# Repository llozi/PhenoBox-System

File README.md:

# Fork of the original PhenoBox-System repo of the Gregor-Mendel-Institute
[Original Repo](https://github.com/Gregor-Mendel-Institute/PhenoBox-System "PhenoBox-System, Gregor-Mendel-Institute")

Changes include the design of a printed circuit board to interface the Raspberry Pi (fully electronic,
no electro-mechanical elements) to facilitate the wiring.

The interface board includes a MOSFET switch for controlling the illumination. It may be used to on/off switch 
or even control the illumination intensity using PWM.

The interface board requires a few changes in the assignment of the GPIO lines.

A few simple python scripts have been added to test the workings of the interface board.

For more details on the modifications check [this fork's Wiki](https://github.com/llozi/PhenoBox-System/wiki).

Below follows the original README.md.

# PhenoBox-System
The “Phenobox”, a flexible, automated, open-source plant phenotyping solution

This is the home of all the source code for our PhenoBox/PhenoPipe system. 

Original Publication: https://nph.onlinelibrary.wiley.com/doi/abs/10.1111/nph.15129

This project is still under developement and we have already planned many improvements.
If you encounter any problems feel free to contribute to this project and help us create a great open source phenotyping solution.

For further reference please use the Wiki pages of this repository. If you have any issues either use the Github Issue page or write an email to sebastian.seitner@vbcf.ac.at

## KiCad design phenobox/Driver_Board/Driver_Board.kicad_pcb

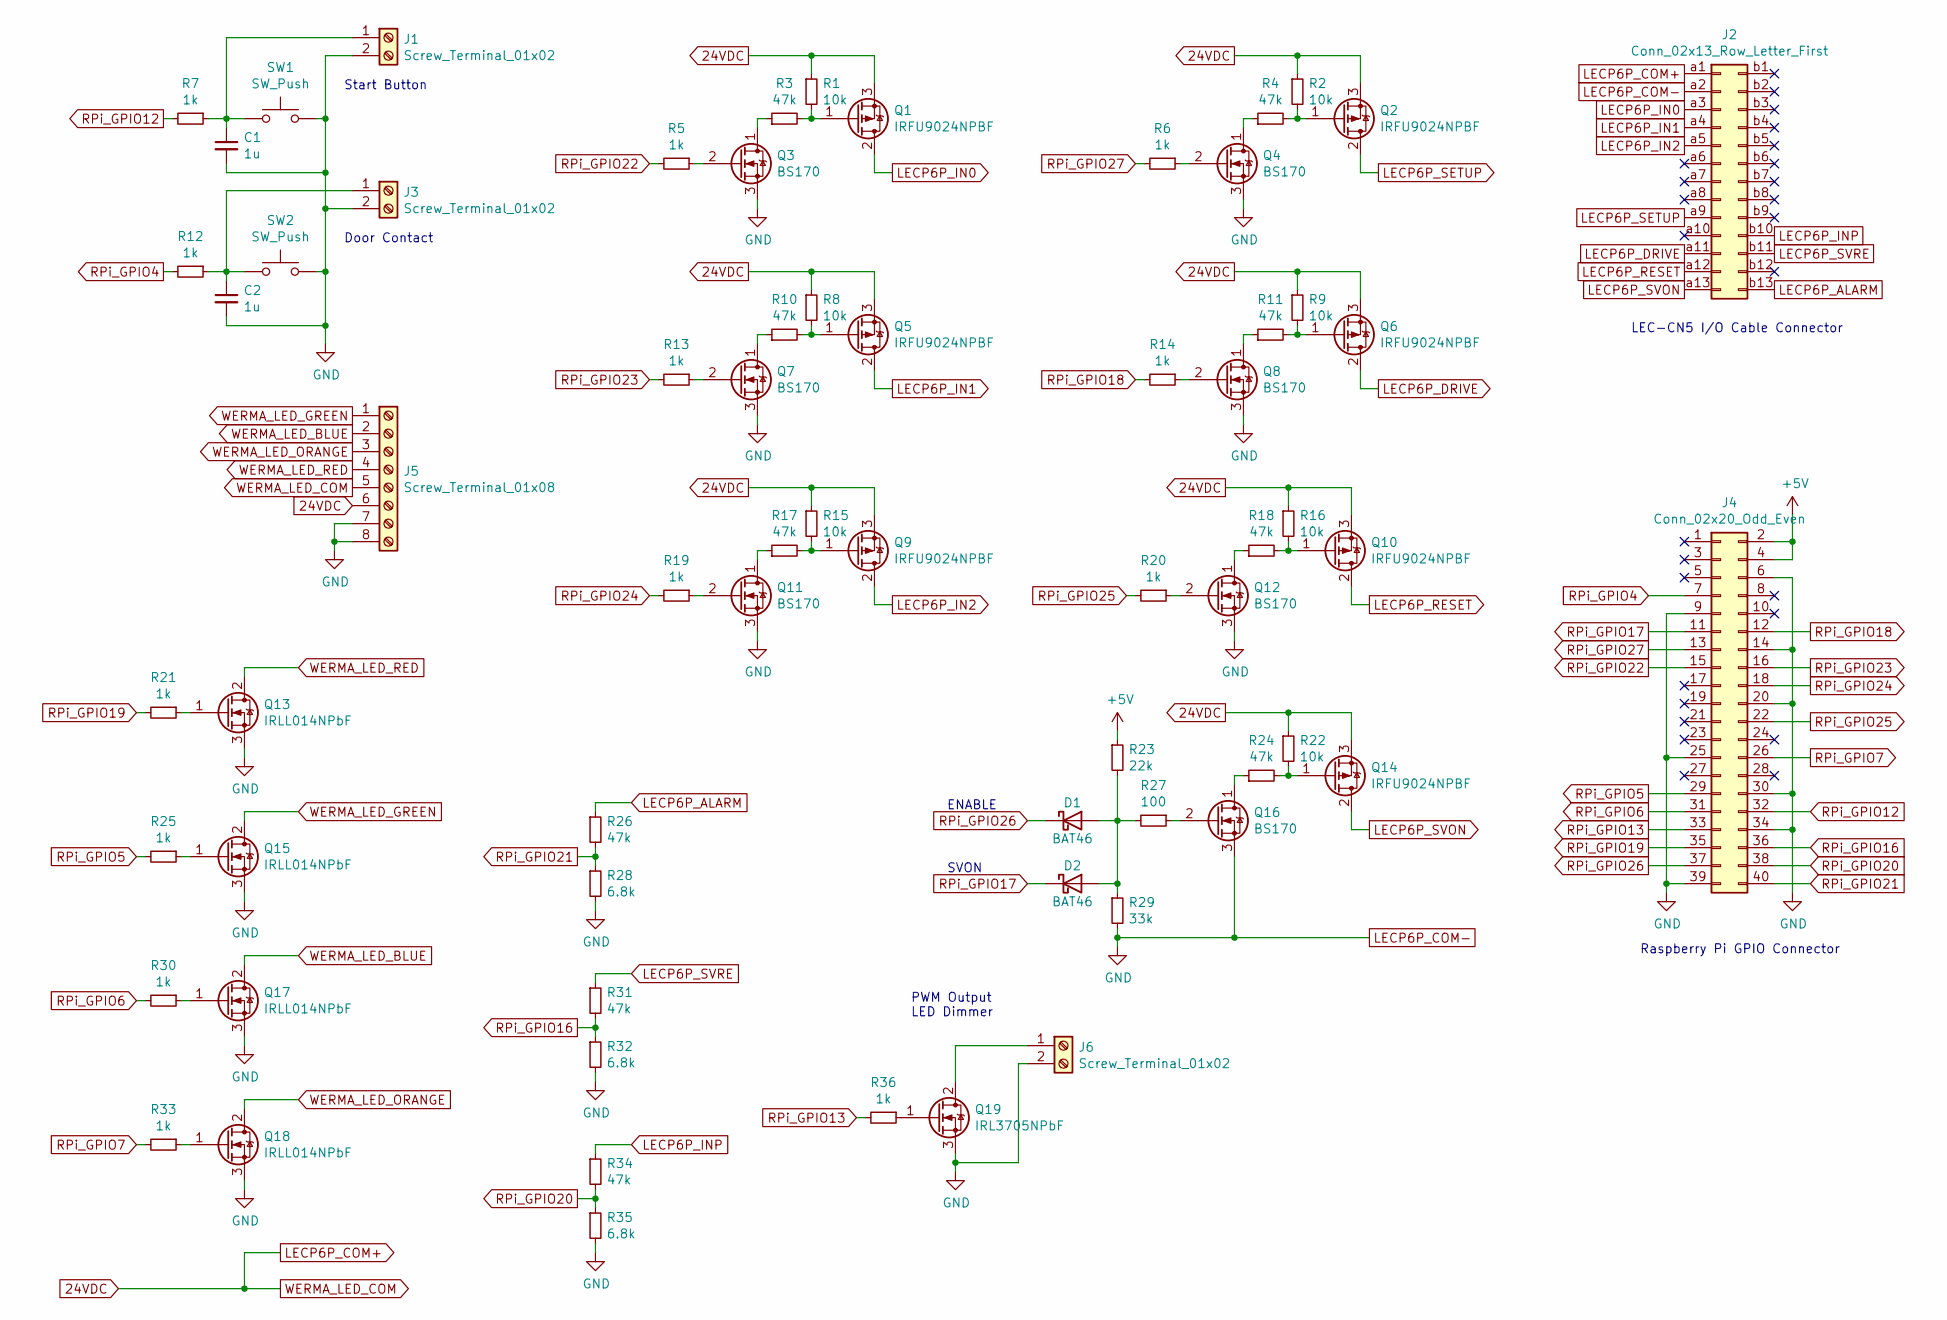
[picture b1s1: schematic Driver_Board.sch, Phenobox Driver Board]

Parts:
C1, C2: 1u; C_Rect_L4.0mm_W2.5mm_P2.50mm
D1, D2: BAT46; D_DO-35_SOD27_P7.62mm_Horizontal
J1, J3, J6: Screw_Terminal_01x02; TerminalBlock_Phoenix_MKDS-1,5-2-5.08_1x02_P5.08mm_Horizont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
J2: Conn_02x13_Row_Letter_First; IDC-Header_2x13_P2.54mm_Vertical
J4: Conn_02x20_Odd_Even; IDC-Header_2x20_P2.54mm_Vertical
J5: Screw_Terminal_01x08; TerminalBlock_Phoenix_MKDS-1,5-8-5.08_1x08_P5.08mm_Horizont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
Q1, Q2, Q5, Q6, Q9, Q10, Q14: IRFU9024NPBF; TO-251-3_Vertical
Q3, Q4, Q7, Q8, Q11, Q12, Q16: BS170; TO-92_Wide
Q13, Q15, Q17, Q18: IRLL014NPbF; SOT-223-3_TabPin2
Q19: IRL3705NPbF; TO-220-3_Vertical
R1, R2, R8, R9, R15, R16, R22: 10k; R_Axial_DIN0207_L6.3mm_D2.5mm_P7.62mm_Horizontal
R3, R4, R10, R11, R17, R18, R24, R26, R31, R34: 47k; R_Axial_DIN0207_L6.3mm_D2.5mm_P7.62mm_Horizontal
R5, R6, R7, R12, R13, R14, R19, R20, R21, R25, R30, R33, R36: 1k; R_Axial_DIN0207_L6.3mm_D2.5mm_P7.62mm_Horizontal
R23: 22k; R_Axial_DIN0207_L6.3mm_D2.5mm_P7.62mm_Horizontal
R27: 100; R_Axial_DIN0207_L6.3mm_D2.5mm_P7.62mm_Horizontal
R28, R32, R35: 6.8k; R_Axial_DIN0207_L6.3mm_D2.5mm_P7.62mm_Horizontal
R29: 33k; R_Axial_DIN0207_L6.3mm_D2.5mm_P7.62mm_Horizontal
SW1, SW2: SW_Push

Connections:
24VDC: J2.a1, J5.5, J5.6, Q1.3 (S), Q2.3 (S), Q5.3 (S), Q6.3 (S), Q9.3 (S), Q10.3 (S), Q14.3 (S), R1.1, R2.1, R8.1, R9.1, R15.1, R16.1, R22.1
+5V: J4.2, J4.4, R23.1
LECP6P_ALARM: J2.b13, R26.1
LECP6P_COM-: C1.2, C2.2, J1.2, J2.a2, J3.2, J4.6, J4.9, J4.14, J4.20, J4.25, J4.30, J4.34, J4.39, J5.7, J5.8, J6.2, Q3.3 (S), Q4.3 (S), Q7.3 (S), Q8.3 (S), Q11.3 (S), Q12.3 (S), Q13.3 (S), Q15.3 (S), Q16.3 (S), Q17.3 (S), Q18.3 (S), Q19.3 (S), R28.2, R29.2, R32.2, R35.2, SW1.2, SW2.2
LECP6P_DRIVE: J2.a11, Q6.2 (D)
LECP6P_IN0: J2.a3, Q1.2 (D)
LECP6P_IN1: J2.a4, Q5.2 (D)
LECP6P_IN2: J2.a5, Q9.2 (D)
LECP6P_INP: J2.b10, R34.1
LECP6P_RESET: J2.a12, Q10.2 (D)
LECP6P_SETUP: J2.a9, Q2.2 (D)
LECP6P_SVON: J2.a13, Q14.2 (D)
LECP6P_SVRE: J2.b11, R31.1
unnamed: C1.1, J1.1, R7.1, SW1.1
unnamed: C2.1, J3.1, R12.1, SW2.1
unnamed: D1.2 (A), D2.2 (A), R23.2, R27.2, R29.1
unnamed: J6.1, Q19.2 (D)
unnamed: Q1.1 (G), R1.2, R3.2
unnamed: Q2.1 (G), R2.2, R4.2
unnamed: Q3.1 (D), R3.1
unnamed: Q3.2 (G), R5.1
unnamed: Q4.1 (D), R4.1
unnamed: Q4.2 (G), R6.1
unnamed: Q5.1 (G), R8.2, R10.2
unnamed: Q6.1 (G), R9.2, R11.2
unnamed: Q7.1 (D), R10.1
unnamed: Q7.2 (G), R13.1
unnamed: Q8.1 (D), R11.1
unnamed: Q8.2 (G), R14.1
unnamed: Q9.1 (G), R15.2, R17.2
unnamed: Q10.1 (G), R16.2, R18.2
unnamed: Q11.1 (D), R17.1
unnamed: Q11.2 (G), R19.1
unnamed: Q12.1 (D), R18.1
unnamed: Q12.2 (G), R20.1
unnamed: Q13.1 (G), R21.1
unnamed: Q14.1 (G), R22.2, R24.2
unnamed: Q15.1 (G), R25.1
unnamed: Q16.1 (D), R24.1
unnamed: Q16.2 (G), R27.1
unnamed: Q17.1 (G), R30.1
unnamed: Q18.1 (G), R33.1
unnamed: Q19.1 (G), R36.1
RPi_GPIO4: J4.7, R12.2
RPi_GPIO5: J4.29, R25.2
RPi_GPIO6: J4.31, R30.2
RPi_GPIO7: J4.26, R33.2
RPi_GPIO12: J4.32, R7.2
RPi_GPIO13: J4.33, R36.2
RPi_GPIO16: J4.36, R31.2, R32.1
RPi_GPIO17: D2.1 (K), J4.11
RPi_GPIO18: J4.12, R14.2
RPi_GPIO19: J4.35, R21.2
RPi_GPIO20: J4.38, R34.2, R35.1
RPi_GPIO21: J4.40, R26.2, R28.1
RPi_GPIO22: J4.15, R5.2
RPi_GPIO23: J4.16, R13.2
RPi_GPIO24: J4.18, R19.2
RPi_GPIO25: J4.22, R20.2
RPi_GPIO26: D1.1 (K), J4.37
RPi_GPIO27: J4.13, R6.2
WERMA_LED_BLUE: J5.2, Q17.2 (D)
WERMA_LED_GREEN: J5.1, Q15.2 (D)
WERMA_LED_ORANGE: J5.3, Q18.2 (D)
WERMA_LED_RED: J5.4, Q13.2 (D)

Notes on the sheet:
Start Button
Door Contact
SVON
ENABLE
LEC-CN5 I/O Cable Connector
Raspberry Pi GPIO Connector
PWM Output LED Dimmer

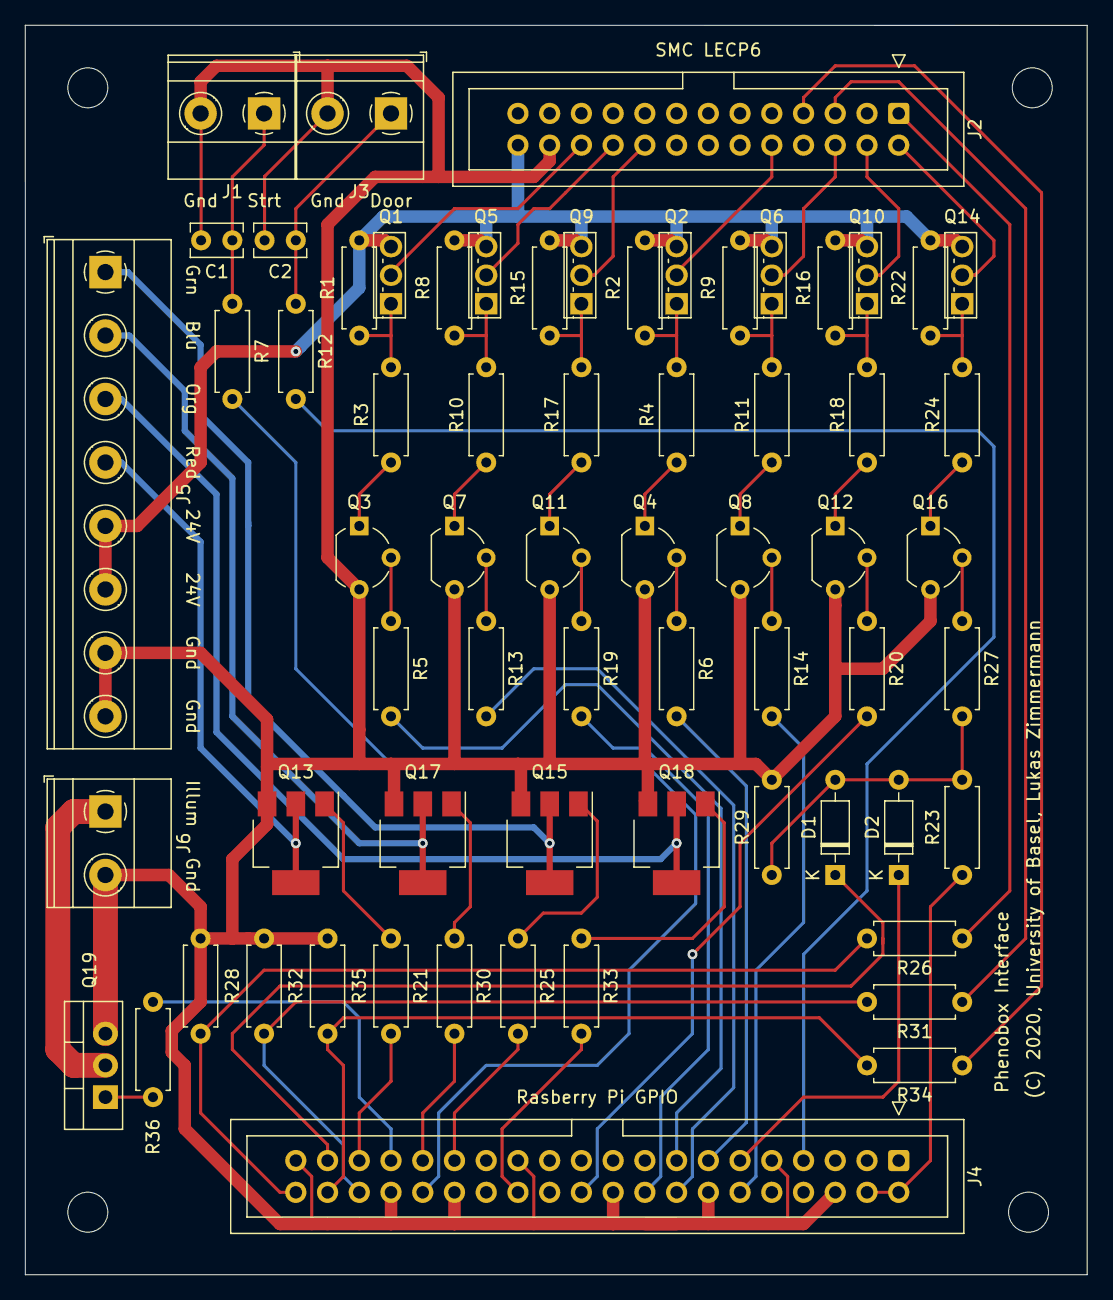
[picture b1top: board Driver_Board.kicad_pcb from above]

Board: 2 copper layers, 85.0 x 100.0 mm, 65 parts (0 on the bottom side), 65 nets.

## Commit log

2020-12-11 In led_controller.py: changed gpio assignments to match the freshly designed "PhenoBox Driver Board".
2020-12-11 Created a few simple scripts for testing the hardware.
2020-12-13 Added a few remarks to the root README.md about the changes of this fork in respect to the original.
2020-12-13 Added the KiCad project of the interface pcb to the Raspberry Pi.
2020-12-16 Added file test_config.ini containing a few settings used for the hardware test scripts.
2020-12-16 In motor_controller.py: removed pulldowns in GPIO inputs. Added a few pint statement (commented out) for debugging. Added line breaks to comments to limit the width of texts.
2020-12-16 In input_controller.py: fixed InputController.evaluate_start() to reliably detect start button pressed and to suppress spurious button releases. I don't know, why the original code does not work reli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
2020-12-16 In test_inputs.py: added logging to be able to better debugging it, includes reading of config file.
2020-12-16 test_motor.py: use gpio_controllers MotorController class, cycle through 6 rotary table positions.
2020-12-16 Created new directory LER10K_LECP6 containing the files with the parameter settings and the step data for the LER10K rotary table.
2020-12-17 Fixed camera/errors.py: if CameraError exception has no "detail" attribute the stringyfied exception produced a runtime error.
2020-12-17 In config/test_config.ini: added "camera_position = vis.side"
2020-12-17 Created super simple script for testing camera: test_camera.py
2020-12-18 In hardware_tests/illu_dim.py: Added correct description to the ArgumentParser. Added copyright notice.
2020-12-18 In hardware_tests/illu_dim.py: fixed unescaped "'" in string.
2020-12-22 Update README.md
    Added link to this fork's github Wiki.
2020-12-30 autostart.py was not working: There is no module photobox, phenobox seems to be meant; The Phenobox class needs to be instantiated. Changed the configuration file name to 'production_config.ini'.
2021-01-18 Added logging to network/token_auth.py.
2021-01-18 Changed imports of package camera to be usable from outside (for hardware_tests/test_camera.py). To test_camera.py, added QR code test scanning.
2021-01-18 Created phenobox_standalone; ported to python3 (3.7.3), removed all code using a remote server to make a version of phenobox usable without server. Made a few improvements, like handling SIG_USR1 to 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
2021-01-18 Changed image_handler.py to do a copy of the original camera file to a subdirectory where the preprocessed images get stored. Removed the networking related exceptions.
2021-01-18 statemachine.py: removed the copying of the originals camera files as this is done in image_handler, now. Added a delay when switching on illumination, to make shure it is at full brightness when the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
2021-01-18 Added and example_config.ini to the phenobox_standalone files.
2021-01-22 statemachine.py: use QR-code data to set plant.experiment_name, plant.sample_group_name, self.plant.name; add error 12: "QR-Code has unknown meaning" indicating improper QR-code data.
2021-01-22 phenobox_standalone.py: import subprocess to be able to shutdown RPi. Use new "preproc_image_folder" config attribute instead of "shared_folder_mountpoint" as place to store preprocessed images (incl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
2021-01-22 image_handler.py: Use new "preproc_image_folder" config attribute instead of "shared_folder_mountpoint" as place to store preprocessed images (incl. originals).
2021-01-22 example_config.ini: added new "preproc_image_folder" config attribute.
2021-01-27 Changed image_handler.py and statemachine.py to use four QR-code fields for experiment (project), time point, treatment and replicate which then is translated to directory struvture and image file na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

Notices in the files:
phenobox/Driver_Board/Driver_Board.kicad_pcb:
(C) 2020, University of Basel, Lukas Zimmermann
